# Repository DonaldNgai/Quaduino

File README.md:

# Quaduino

A quadcopter controlled by an Arduino Uno capable of automated hovering.

## Parts
**Frame** - https://www.hobbyking.com/hobbyking/store/uh_viewItem.asp?idProduct=66628

**Batteries** - https://www.hobbyking.com/hobbyking/store/uh_viewItem.asp?idProduct=8934

**Motors and Propellers** - https://www.hobbyking.com/hobbyking/store/uh_viewItem.asp?idProduct=43884

**Power Distribution Board** - https://www.hobbyking.com/hobbyking/store/uh_viewItem.asp?idProduct=23140

**Electronic Speed Controllers (ESC's)** - https://www.hobbyking.com/hobbyking/store/uh_viewItem.asp?idProduct=58264

**Charger** - https://www.hobbyking.com/hobbyking/store/uh_viewItem.asp?idProduct=49338

###Controller (IMU)
**Arduino UNO** - https://www.arduino.cc/en/Main/ArduinoBoardUno

**Accelerometer and Gyroscope (MPU6050)** - http://www.ebay.com/itm/6DOF-MPU-6050-Module-3-Axis-Gyroscope-Accelerometer-Module-for-Arduino-MPU-6050-/381374932942?

**Barometer (BMP180)** - http://www.ebay.com/itm/BMP180-Replace-BMP085-Digital-Barometric-Pressure-Sensor-Board-Module-Arduino-/261719866003?ssPageName=ADME:L:OU:CA:3160

###Communication
**Bluetooth receiver (HC06)** - http://www.ebay.com/itm/Wireless-Serial-4-Pin-Bluetooth-RF-Transceiver-Module-HC-06-RS232-With-backplane-/200924726178?ssPageName=ADME:X:RRIRTB:US:3160

**Android Phone** - I used an HTC One M8

## Installation

1.	Make sure the quadcopter is wired correctly based on the diagram shown here.
2.	Upload the Arduino code onto the Arduino.
3.	Install the application onto an Android device.

## Usage

###Changing PID values
1.	Return to the main screen on the Android application
2.	Reset the Arduino UNO by pressing the reset button onboard
3.	Wait 2 seconds
4.	Click on "Set Values"
5.	The LED should light up if this was done correctly, if not, exit back to the main screen and repeat step 4.
6.	Set the PID values and then click the "Send Values" button
IMPORTANT: Only set up to 3 PID values at once to be safe
7.	If the values were successfully set, the ESC's will now be armed and thus will make a noise.

###Operating the Quadcopter
1.	Check the "Arm" checkbox. The ESC's should arm themselves and make a noise.
2.	At this point, changing the power slider will not take effect as the "Power" checkbox is unchecked. It is recommended to make sure the power slider is at 0.
3.	Check the "Power" checkbox to gain control of the power of the motors
4.	Check the "Control" checkbox if you wish to control the quadcopter using the phone's orientation. It is recommended to click the "Calibrate" button before this to set the current orientation of the phone as the neutral position.

If either the "Arm" or "Power" checkboxes are unchecked during flight, the Quadcopter will enter into hover mode.

## Credits

###Software Used:
**Arduino** - https://www.arduino.cc/en/Main/Software

**MIT App Inventor 2** - http://ai2.appinventor.mit.edu/

**Eagle PCB Design Software** - http://www.cadsoftusa.com/download-eagle/?CMP=KNC-GUS-FUS-GEN-SUP-CAD-Eeagle

###Tutorials Used/Code Used:
**Hardware Reference** - http://www.instructables.com/id/DIY-ARDUINO-FLIGHT-CONTROLLER/
http://forum.arduino.cc/index.php?topic=184503.0

**Testing MPU6050** - http://diyhacking.com/arduino-mpu-6050-imu-sensor-tutorial/
http://playground.arduino.cc/Main/MPU-6050
https://www.sparkfun.com/products/11028

**Testing BMP180** - https://learn.sparkfun.com/tutorials/bmp180-barometric-pressure-sensor-hookup-

**IMU and PID code reference** - https://github.com/baselsw/BlueCopter

**ESC and Motor operation** - http://www.instructables.com/id/ESC-Programming-on-Arduino-Hobbyking-ESC/
http://forum.arduino.cc/index.php?topic=20184.0

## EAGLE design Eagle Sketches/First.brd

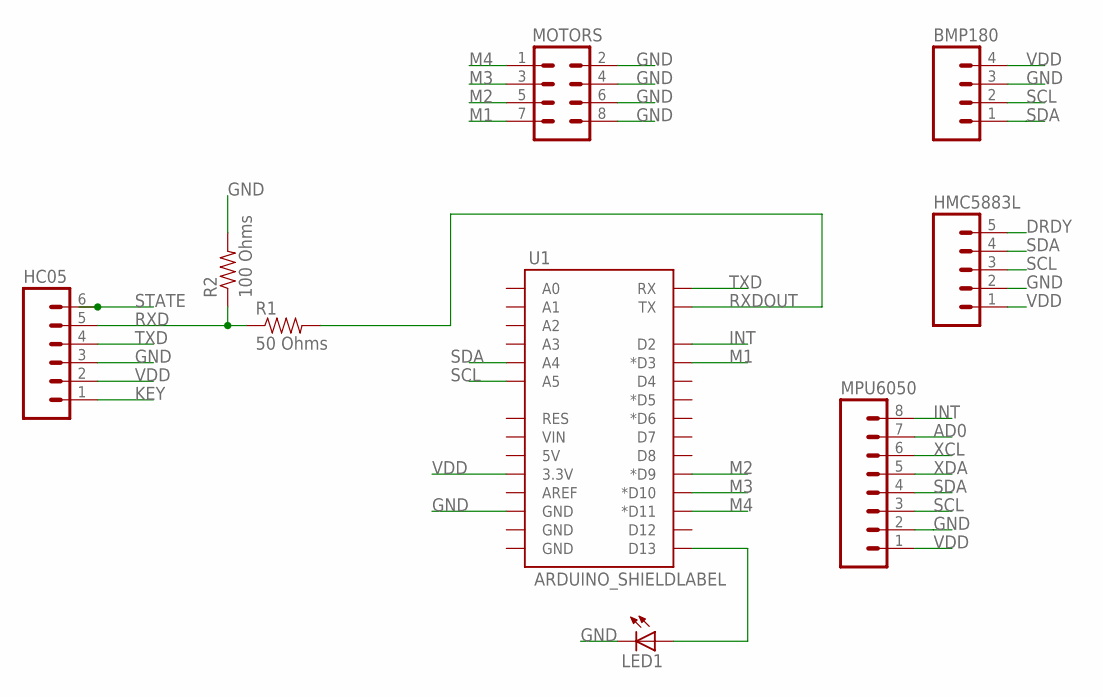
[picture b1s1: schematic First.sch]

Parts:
BMP180: M04PTH; 1X04
HC05: M06NO_SILK_FEMALE_PTH; 1X06_NO_SILK
HMC5883L: M05_ROUNDONLY_NOSILK; 1X05_ROUNDONLY_NOSILK
LED1: LED5MM
MOTORS: M04X2; 2X4
MPU6050: M08NO_SILK; 1X08_PIN1_NO_SILK
R1: 50 Ohms; SPARKFUN_AXIAL-0.3
R2: 100 Ohms; SPARKFUN_AXIAL-0.3
U1: ARDUINO_SHIELDLABEL; DUEMILANOVE_SHIELD

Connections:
AD0: MPU6050.7
DRDY: HMC5883L.5
GND: BMP180.3, HC05.3, HMC5883L.2, LED1.K (C), MOTORS.2, MOTORS.4, MOTORS.6, MOTORS.8, MPU6050.2, R2.P$2 (2), U1.GND@2 (GND)
INT: MPU6050.8, U1.D2
KEY: HC05.1
M1: MOTORS.7, U1.D3 (*D3)
M2: MOTORS.5, U1.D9 (*D9)
M3: MOTORS.3, U1.D10 (*D10)
M4: MOTORS.1, U1.D11 (*D11)
unnamed: LED1.A, U1.D13
RXD: HC05.5, R1.P$1 (1), R2.P$1 (1)
RXDOUT: R1.P$2 (2), U1.TX
SCL: BMP180.2, HMC5883L.3, MPU6050.3, U1.A5
SDA: BMP180.1, HMC5883L.4, MPU6050.4, U1.A4
STATE: HC05.6
TXD: HC05.4, U1.RX
VDD: BMP180.4, HC05.2, HMC5883L.1, MPU6050.1, U1.3.3V
XCL: MPU6050.6
XDA: MPU6050.5

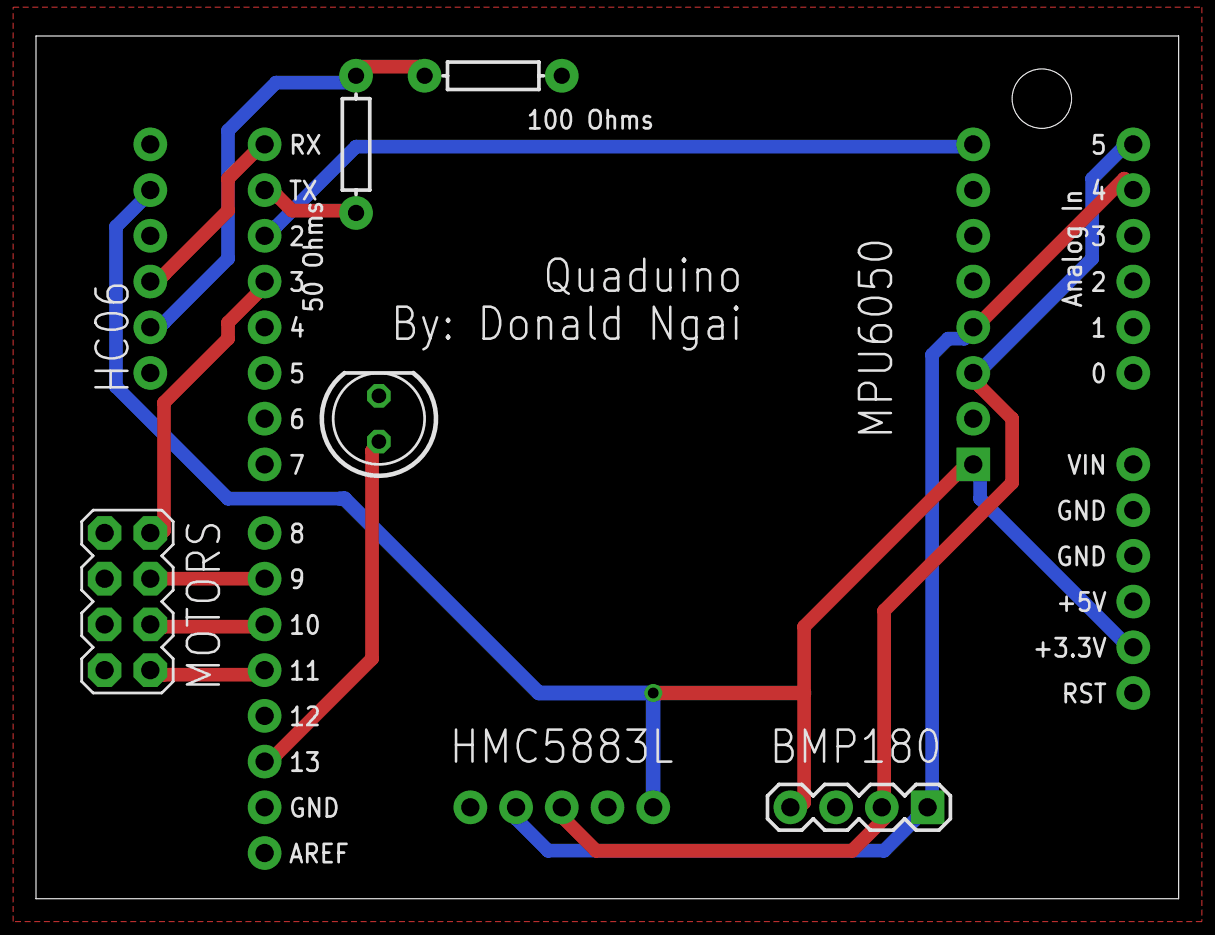
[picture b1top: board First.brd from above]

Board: 2 copper layers, 63.5 x 47.9 mm, 9 parts (0 on the bottom side), 13 nets.

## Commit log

2015-10-06 Added Recordings of Problems
2015-10-07 Fixed setting PID values from bluetooth to receive data correctly. Added in the ability to receive max and min of PID values. Need to add in receiving Yaw sensor data and add in HMC5883L
2016-01-01 Removed BMP, changed PID values, and fixed compensating not getting to all motors
2016-03-12 Updated to latest code from home computer
2016-03-15 Added android app made from android studio
2016-03-15 Made flight controller full screen work nicely
2016-03-15 Added button compatibility and debug screen and sensor acquisition
2016-03-15 Having trouble calibrating yaw
2016-03-16 Done except changing hard coded values, refactoring and making sure phone calibration is working
2016-03-16 added in throttle to data string
2016-03-16 Made throttle only work if arm and begin are checked
2016-03-19 Changed up to allow for arduino to notify that it is stable
2016-03-20 Changed bluetooth receive function and changed the frequency that the DMP computes data and changed the MPU function to make it stop freezing up
2016-03-21 Added in change pid flag, fixed changing PID code, removed a lot of debugging print statements works really well!
2016-03-21 Changed order or bluetooth data, i think i changed it to 50Hz, added ChangePID flag
2016-03-21 Made it go back to hover when I stop controlling it, changed the order of the bluetooth data
2016-03-22 Missing semi colon
2016-03-22 fixed up calibrating drone button
2016-03-22 fixed calibrating and now just need to make android application remove old text to not slow it down
2016-03-23 Made old lines of textview get deleted
2016-03-23 Made setY,setP,setR into type float
2016-04-02 Need to recalibrate the offsets for MPU, changed starting PID values, removed some commented out code, added code to set YPR after waiting for MPU to stabilize
2016-04-23 Changed the offsets
2016-04-23 Removed Todo statements
2016-04-23 Got a bit more working
    Still not sure why adding in serial print lines make the controller work
    but it does. Also, I have a suspicion that the smoothed values are
    causing problems so i am outputting what the smoothed value is. Lastly,
    i want to try again at calibrating the ESC's in hope that it will fix
    the one motor being stronger problem.
2016-04-23 Change PID start values. These values were pretty good
2016-04-24 Need to fix sensor jumps, need to make sure android YPR is accurate
    Made debug screen smaller on android, calibrated esc so that fixed
    problem of one motor being stronger than others. I also changed from
    analog write to using the servo library .write function.
2016-04-24 Fixed phone yaw,pitch,roll
2016-04-25 Fixed sensor jumps, and removed flagged for mpu interrupt which increased data speed(good)
    There was a static int inside the smoothing function so all the yaw
    pitch and roll smoothing calls were all referring to the same int so as
    a result, only 3/9 of the places in the array was ever used. I changed
    that and now that should also smooth out any spikes
2016-04-25 Added Fail detection
2016-04-30 Added in failsafe, changed PID value a bit, added getActivityForResult in android, added eagle sketches
2016-05-01 Added in checksum, changed PID value a bit, changed layout of android app so that it shows what it is sending currently
2016-05-17 Made seekbar draggable but need to account for edge case where i click with 10 of original but boxes aren't checked
2016-05-17 Included the folder of libraries needed to be installed with arduino for compilation
2016-05-18 Refactored some code to make it local variables to free up some SRAM, also, added in functionality to limit frequency of PID caluclations
2016-05-18 Removed libraries folder
2016-05-19 Variable changes
2016-06-01 Changed yaw error so it doesn't jump when it goes from -180 to 180
2016-06-14 Did stuff, i don't remember actually...
2016-06-14 Changed offsets and changed PID value
2016-07-15 Made quite a few changes, can't even remember now
2016-07-15 Changed write to write microseconds and checked speed of main loop
2016-07-15 Changed starting and stopping values based on microseconds
2016-07-15 Forgot to update timeChange before while loop
2016-07-17 Changed max pid values
2016-08-14 Changes after Asking for Help
    Changed Main Loop flow
    Changed Millis to Micros
    Changed smoothing library to only calculate ints
    Added Scaling for DMP values
2016-08-16 Got 600 Hz Fast Loop!!!
    Changed main loop to contain fast and slow loop
    Updated retrieving DMP logic as well as placed smoothing in that
    function
    Made Bluetooth more consistent by implementing if statement
    Removed Print statements
    Added in ability to read gyro data
2016-08-19 Got rid of crashing
    Removed usage of DMP
    Instead, uses complimentary filter now using raw accel and gyro values
    to determine orientation
    need a filter for accel data
    PID results are acting weird, gotta check it out
2016-09-06 Changes to Android to support new rate loop
    Changes to android and stuff
2016-09-06 Added debug flag
2016-09-26 Changed smoothing and also fixed it so taht it actually uses the right buffer size
2016-09-26 Made change to show scroll lock again on phone
2016-09-27 Made graphic changes to android app, divided raw gyro by sensitivity, changed pid
2016-09-30 Motor jitter was caused by bad packets, added return statement to not proecess bad packets. PIDroll_val was also flipped
2016-09-30 Added crazy angle failsafe, changed angle pid, still need to add in yaw lock using another angle pid loop
2016-10-12 Orientation calculation was flipped for roll and pitch, changed control pid to use simpled pid function, made sure correct motors were compensating
2016-10-12 changed crazy angle threshold, and switch phone roll and pitch
2016-10-14 added smooth array to the orientation data
2016-11-05 Added in filter for accelerometer data but not working
2017-05-30 Adding LSB sensitivity for accelerometer
2017-05-30 Making temp to a int to conserve space
2017-06-02 Cleaned up gyro code, and added in high pass filter for gyroscope data
2017-06-02 Corrected trig functions to get pitch and roll using accel data
2017-06-02 code refactoring

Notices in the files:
parts and their libraries:
SparkFun-Boards: Licensing: Creative Commons ShareAlike 4.0 International - https://creativecommons.org/licenses/by-sa/4.0
